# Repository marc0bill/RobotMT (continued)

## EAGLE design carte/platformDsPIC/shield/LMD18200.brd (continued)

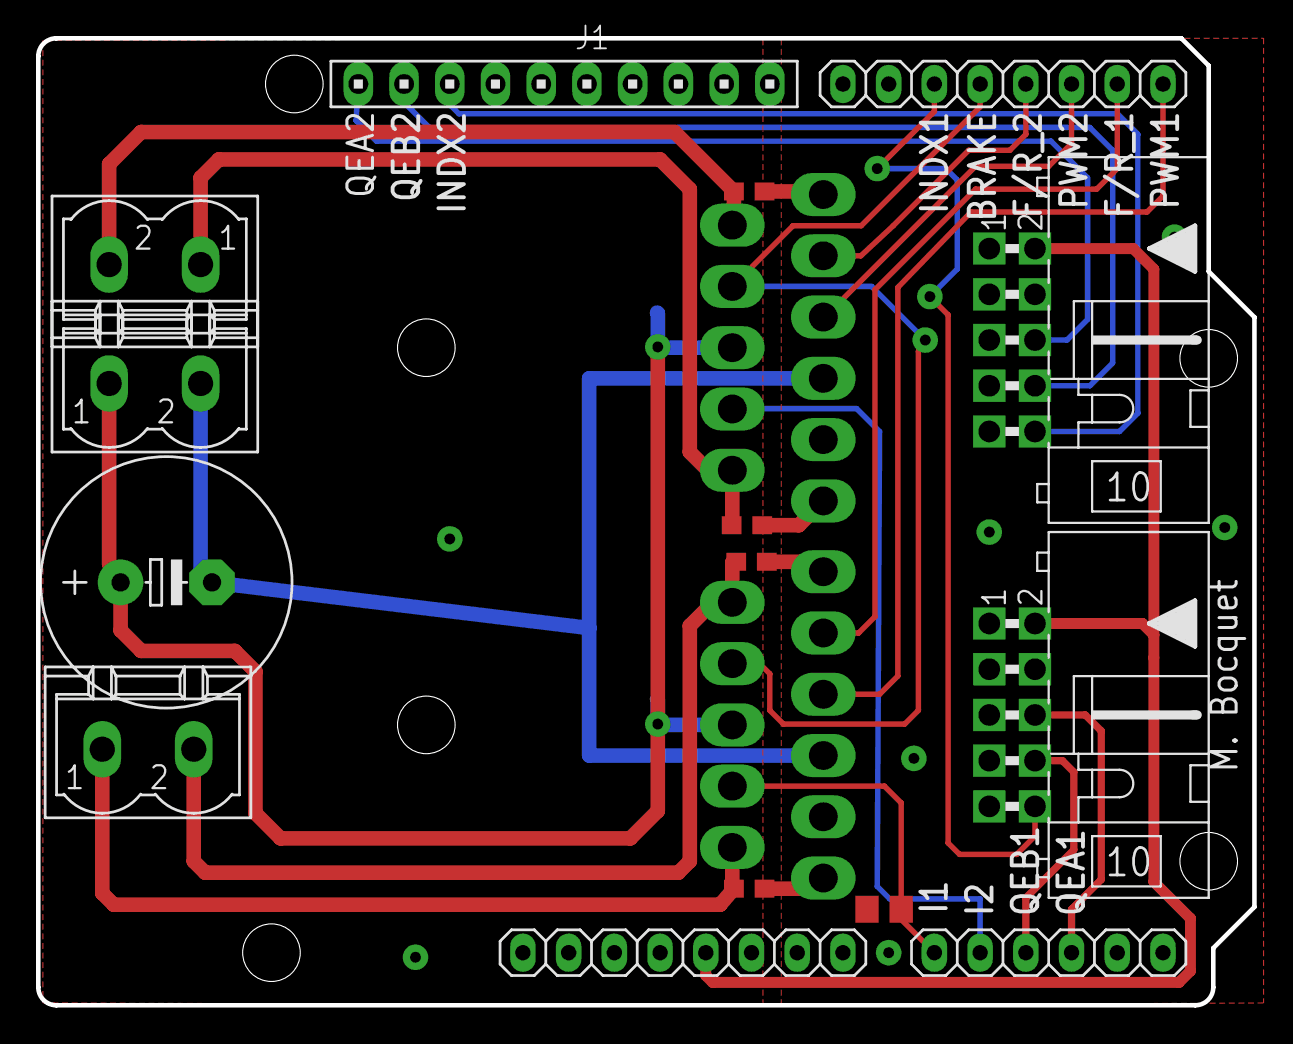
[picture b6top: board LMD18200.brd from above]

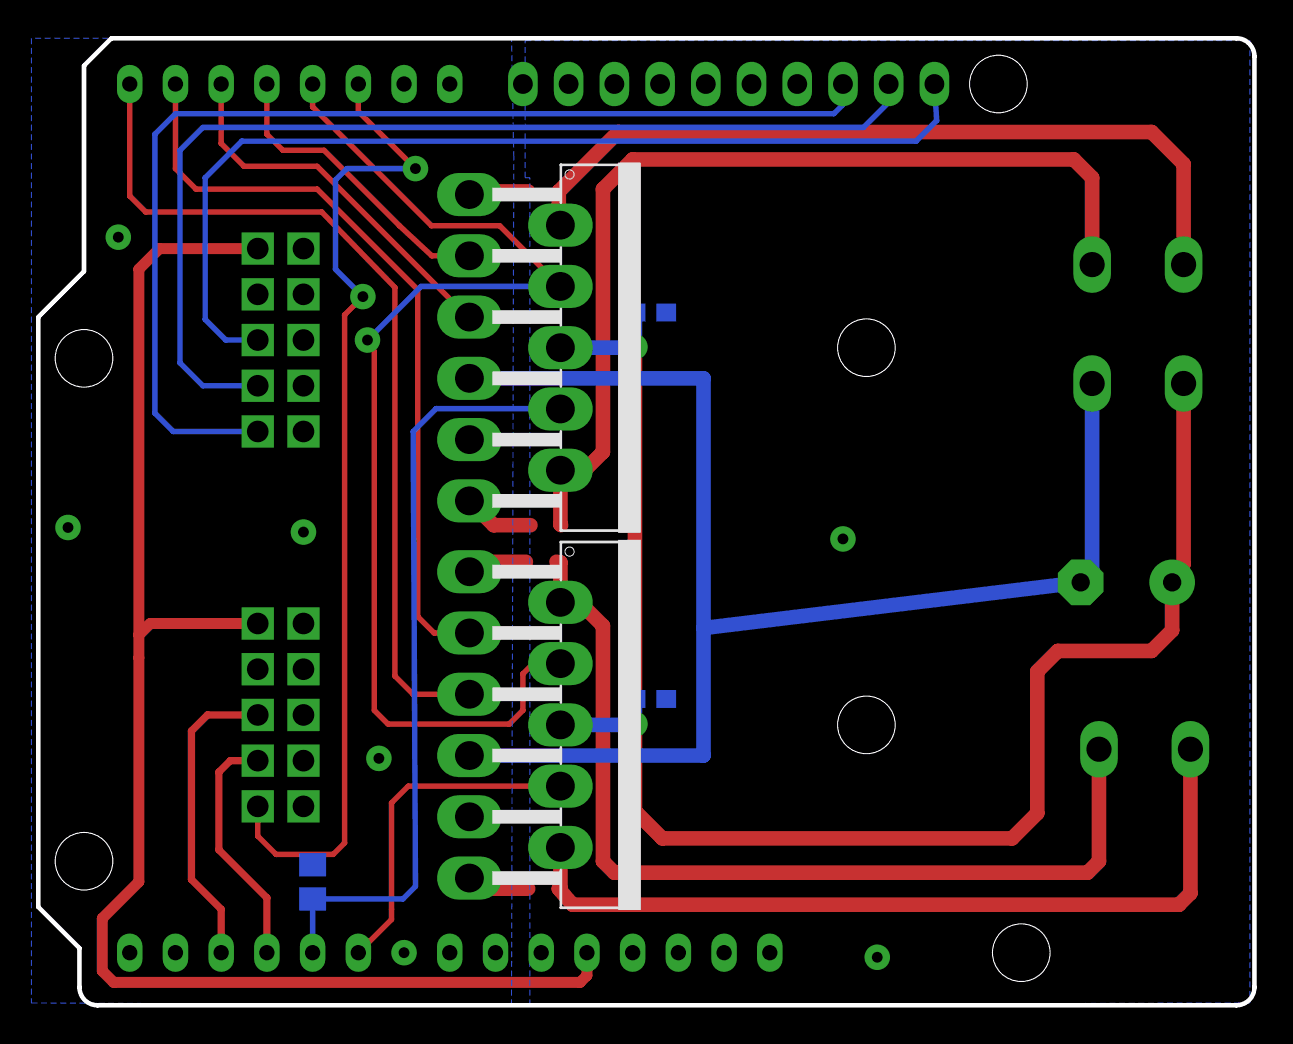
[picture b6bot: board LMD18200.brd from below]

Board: 2 copper layers, 67.6 x 53.7 mm, 20 parts (5 on the bottom side), 25 nets.

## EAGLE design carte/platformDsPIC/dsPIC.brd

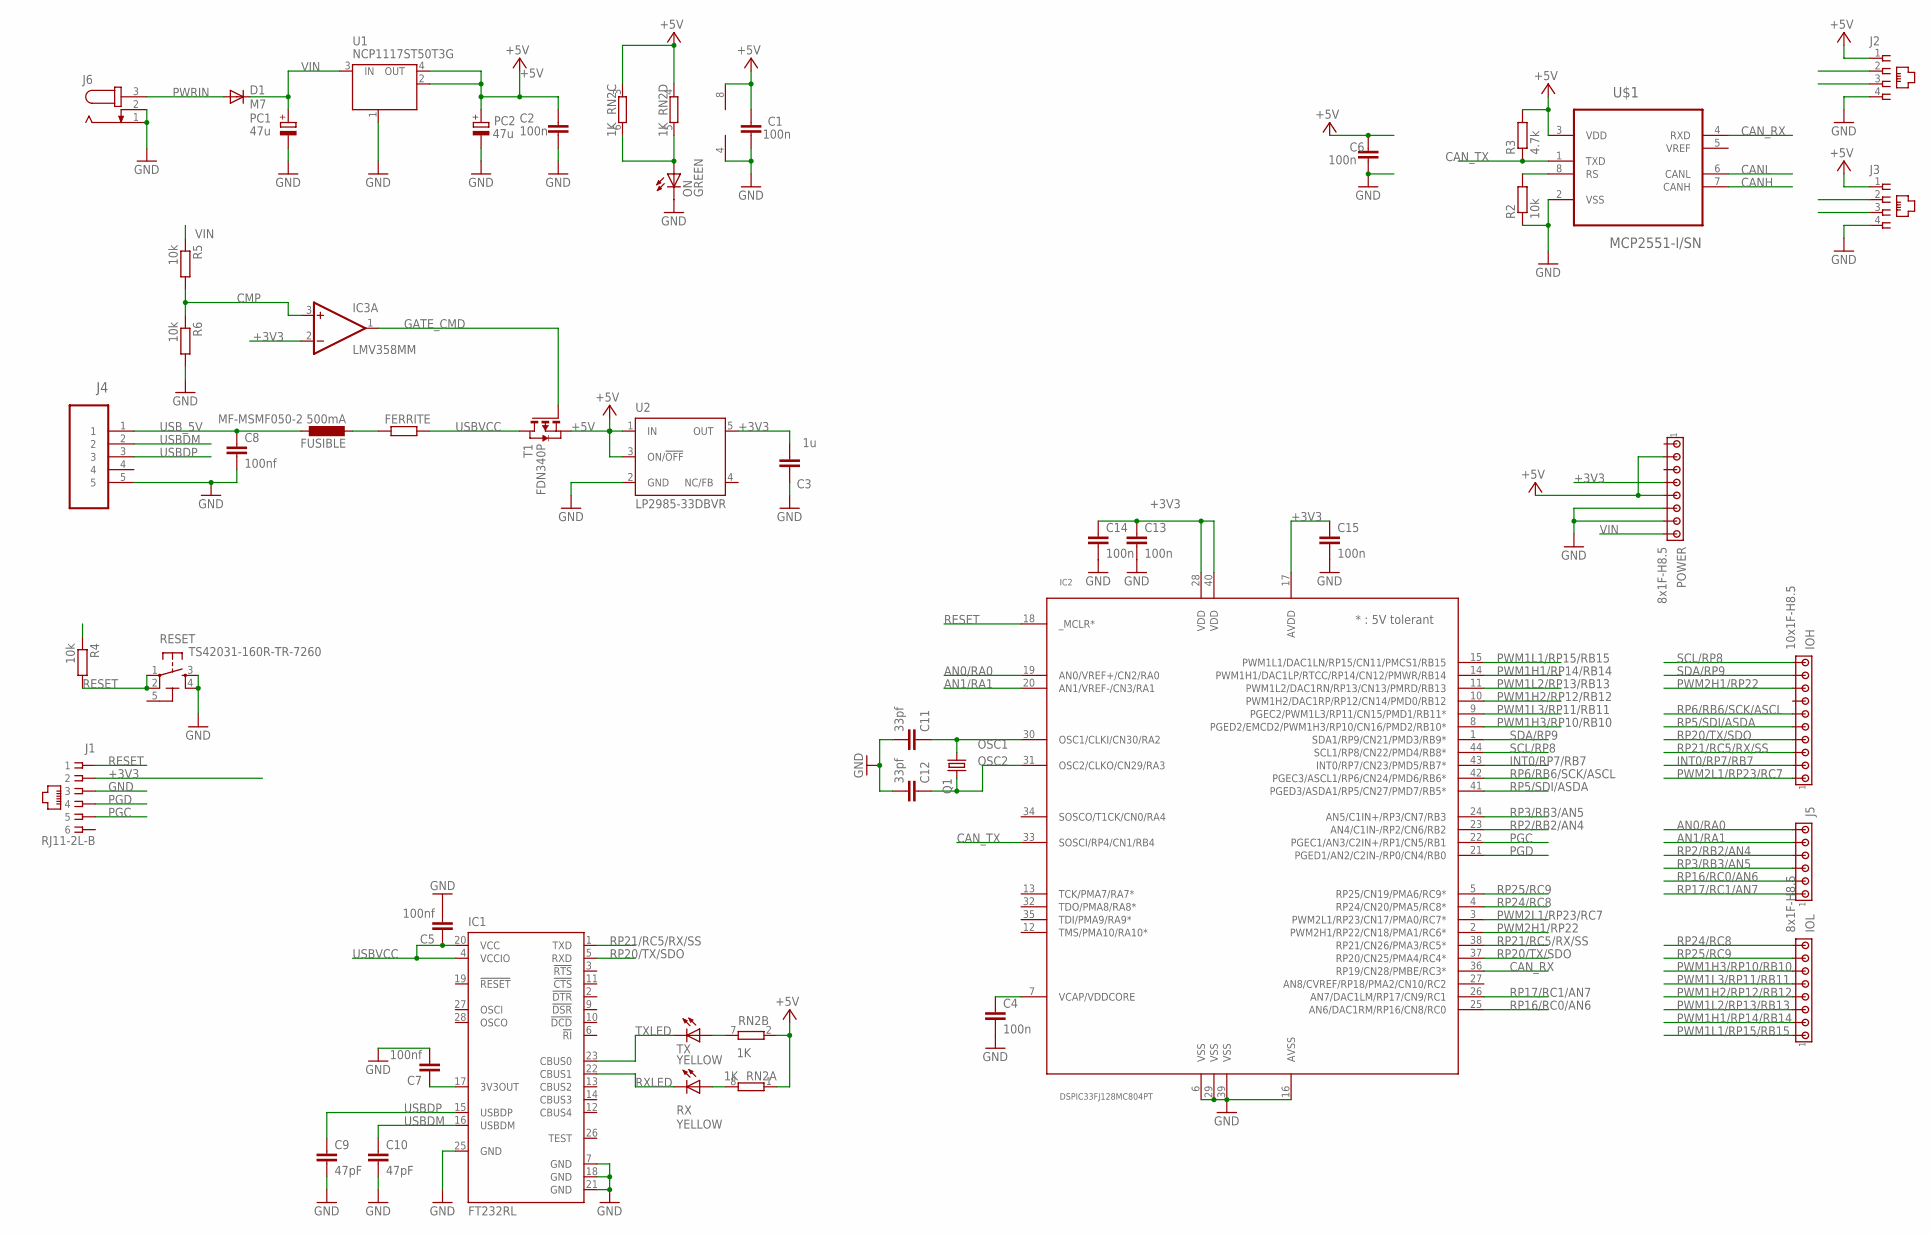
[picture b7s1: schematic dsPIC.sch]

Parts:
C1, C2: 100n; C0603-ROUND
C3: 1u; C0603-ROUND
C4, C6: 100n; C0603K
C5, C7, C8: 100nf; C0603
C9, C10: 47pF; C0603
C11, C12: 33pf; C0603
C13, C14, C15: 100n; C0603
D1: M7; SMB
FERRITE: R-EU_M0805; M0805
FUSIBLE: MF-MSMF050-2 500mA; L1812
IC1: FT232RL; SSOP28
IC2: DSPIC33FJ128MC804PT; TQFP44
IC3: LMV358MM; MSOP08
IOH: 10x1F-H8.5; 10X10MTA
IOL: 8x1F-H8.5; 10X08MTA
J1: RJ11-2L-B; RJ11-NO_SHIELD
J2, J3: 520249-2
J4: 47346-0001; MOLEX_47346-0001
J5: MTA06-100; 10X06MTA
J6: JACK-PLUG0; SPC4077
ON: GREEN; CHIP-LED0805
PC1, PC2: 47u; PANASONIC_D
POWER: 8x1F-H8.5; 10X08MTA
Q1: CRYSTALSM49; SM49
R2, R4, R5, R6: 10k; R0805
R3: 4.7k; R0805
RESET: TS42031-160R-TR-7260; TS42
RN2: 1K; CAY16
RX: YELLOW; CHIP-LED0805
T1: FDN340P; SOT-23
TX: YELLOW; CHIP-LED0805
U1: NCP1117ST50T3G; SOT223
U2: LP2985-33DBVR; SOT23-DBV
U$1: MCP2551-I/SN; SOIC127P600X175-8N

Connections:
5-GND: RESET.5 (5-GND)
+3V3: C3.2, C13.1, C14.1, C15.1, IC2.17 (AVDD), IC2.28 (VDD), IC2.40 (VDD), IC3.2 (-IN), J1.2, POWER.4, R4.1, U2.5 (OUT)
+5V: C1.2, C2.2, C6.2, IC3.8 (V+), J2.1, J3.1, PC2.+, POWER.2, POWER.5, R3.2, RN2.1, RN2.2 (1), RN2.3 (1), RN2.4 (1), T1.2 (S), U1.2 (OUT), U1.4 (OUT), U2.1 (IN), U2.3 (ON/!OFF), U$1.3 (VDD)
AN0/RA0: IC2.19 (AN0/VREF+/CN2/RA0), J5.1 (6)
AN1/RA1: IC2.20 (AN1/VREF-/CN3/RA1), J5.2 (5)
CANH: J2.2, J3.2, U$1.7 (CANH)
CANL: J2.3, J3.3, U$1.6 (CANL)
CAN_RX: IC2.36 (RP19/CN28/PMBE/RC3*), U$1.4 (RXD)
CAN_TX: IC2.33 (SOSCI/RP4/CN1/RB4), R3.1, U$1.1 (TXD)
CMP: IC3.3 (+IN), R5.2, R6.1
GATE_CMD: IC3.1 (OUT), T1.3 (G)
GND: C1.1, C2.1, C3.1, C4.2, C5.2, C6.1, C7.2, C8.2, C9.2, C10.2, C11.2, C12.2, C13.2, C14.2, C15.2, IC1.7 (GND), IC1.18 (GND), IC1.21 (GND), IC1.25 (GND), IC2.6 (VSS), IC2.16 (AVSS), IC2.29 (VSS), IC2.39 (VSS), IC3.4 (V-), J1.3, J2.4, J3.4, J4.5, J6.1, J6.2, ON.C, PC1.-, PC2.-, POWER.6, POWER.7, R2.1, R6.2, RESET.3, RESET.4, U1.1 (GND/ADJ), U2.2 (GND), U$1.2 (VSS)
INT0/RP7/RB7: IC2.43 (INT0/RP7/CN23/PMD5/RB7*), IOH.2
unnamed: RN2.7 (2), TX.A
unnamed: C7.1, IC1.17 (3V3OUT)
unnamed: ON.A, RN2.5 (2), RN2.6 (2)
unnamed: FERRITE.1, FUSIBLE.2
unnamed: C4.1, IC2.7 (VCAP/VDDCORE)
unnamed: RN2.8 (2), RX.A
unnamed: R2.2, U$1.8 (RS)
OSC1: C11.1, IC2.30 (OSC1/CLKI/CN30/RA2), Q1.1
OSC2: C12.1, IC2.31 (OSC2/CLKO/CN29/RA3), Q1.2
PGC: IC2.22 (PGEC1/AN3/C2IN+/RP1/CN5/RB1), J1.5
PGD: IC2.21 (PGED1/AN2/C2IN-/RP0/CN4/RB0), J1.4
PWM1H1/RP14/RB14: IC2.14 (PWM1H1/DAC1LP/RTCC/RP14/CN12/PMWR/RB14), IOL.2
PWM1H2/RP12/RB12: IC2.10 (PWM1H2/DAC1RP/RP12/CN14/PMD0/RB12), IOL.4
PWM1H3/RP10/RB10: IC2.8 (PGED2/EMCD2/PWM1H3/RP10/CN16/PMD2/RB10*), IOL.6
PWM1L1/RP15/RB15: IC2.15 (PWM1L1/DAC1LN/RP15/CN11/PMCS1/RB15), IOL.1
PWM1L2/RP13/RB13: IC2.11 (PWM1L2/DAC1RN/RP13/CN13/PMRD/RB13), IOL.3
PWM1L3/RP11/RB11: IC2.9 (PGEC2/PWM1L3/RP11/CN15/PMD1/RB11*), IOL.5
PWM2H1/RP22: IC2.2 (PWM2H1/RP22/CN18/PMA1/RC6*), IOH.8
PWM2L1/RP23/RC7: IC2.3 (PWM2L1/RP23/CN17/PMA0/RC7*), IOH.1
PWRIN: D1.A, J6.3
RESET: IC2.18 (_MCLR*), J1.1, R4.2, RESET.1, RESET.2
RP2/RB2/AN4: IC2.23 (AN4/C1IN-/RP2/CN6/RB2), J5.3 (4)
RP3/RB3/AN5: IC2.24 (AN5/C1IN+/RP3/CN7/RB3), J5.4 (3)
RP5/SDI/ASDA: IC2.41 (PGED3/ASDA1/RP5/CN27/PMD7/RB5*), IOH.5
RP6/RB6/SCK/ASCL: IC2.42 (PGEC3/ASCL1/RP6/CN24/PMD6/RB6*), IOH.6
RP16/RC0/AN6: IC2.25 (AN6/DAC1RM/RP16/CN8/RC0), J5.5 (2)
RP17/RC1/AN7: IC2.26 (AN7/DAC1LM/RP17/CN9/RC1), J5.6 (1)
RP20/TX/SDO: IC1.5 (RXD), IC2.37 (RP20/CN25/PMA4/RC4*), IOH.4
RP21/RC5/RX/SS: IC1.1 (TXD), IC2.38 (RP21/CN26/PMA3/RC5*), IOH.3
RP24/RC8: IC2.4 (RP24/CN20/PMA5/RC8*), IOL.8
RP25/RC9: IC2.5 (RP25/CN19/PMA6/RC9*), IOL.7
RXLED: IC1.22 (CBUS1), RX.C
SCL/RP8: IC2.44 (SCL1/RP8/CN22/PMD4/RB8*), IOH.10
SDA/RP9: IC2.1 (SDA1/RP9/CN21/PMD3/RB9*), IOH.9
TXLED: IC1.23 (CBUS0), TX.C
USBDM: C10.1, IC1.16 (USBDM), J4.2
USBDP: C9.1, IC1.15 (USBDP), J4.3
USBVCC: C5.1, FERRITE.2, IC1.4 (VCCIO), IC1.20 (VCC), T1.1 (D)
USB_5V: C8.1, FUSIBLE.1, J4.1
VIN: D1.C, PC1.+, POWER.8, R5.1, U1.3 (IN)

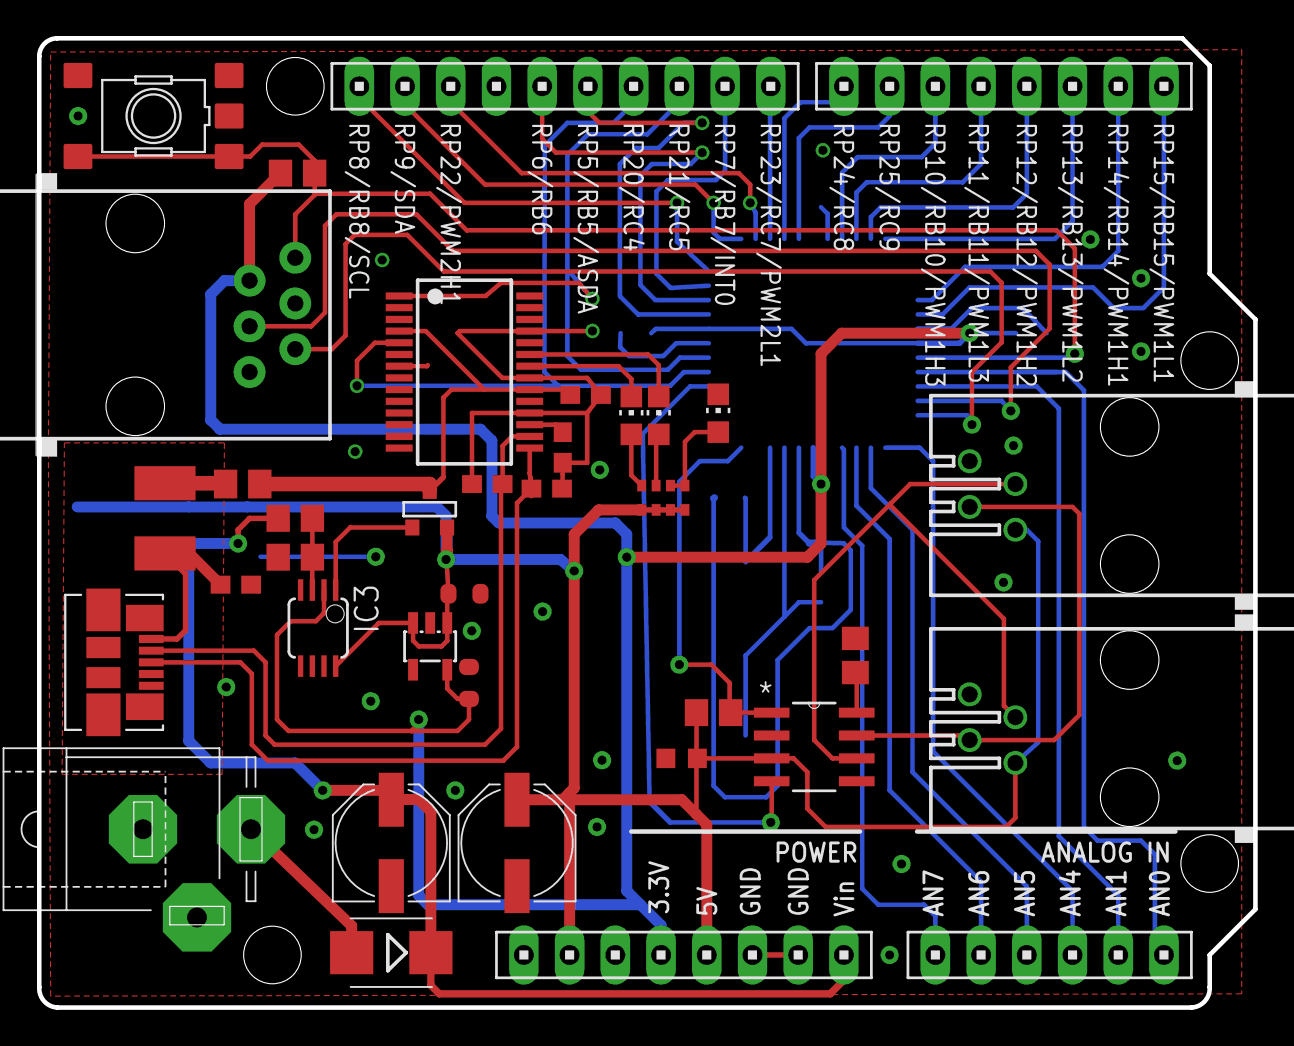
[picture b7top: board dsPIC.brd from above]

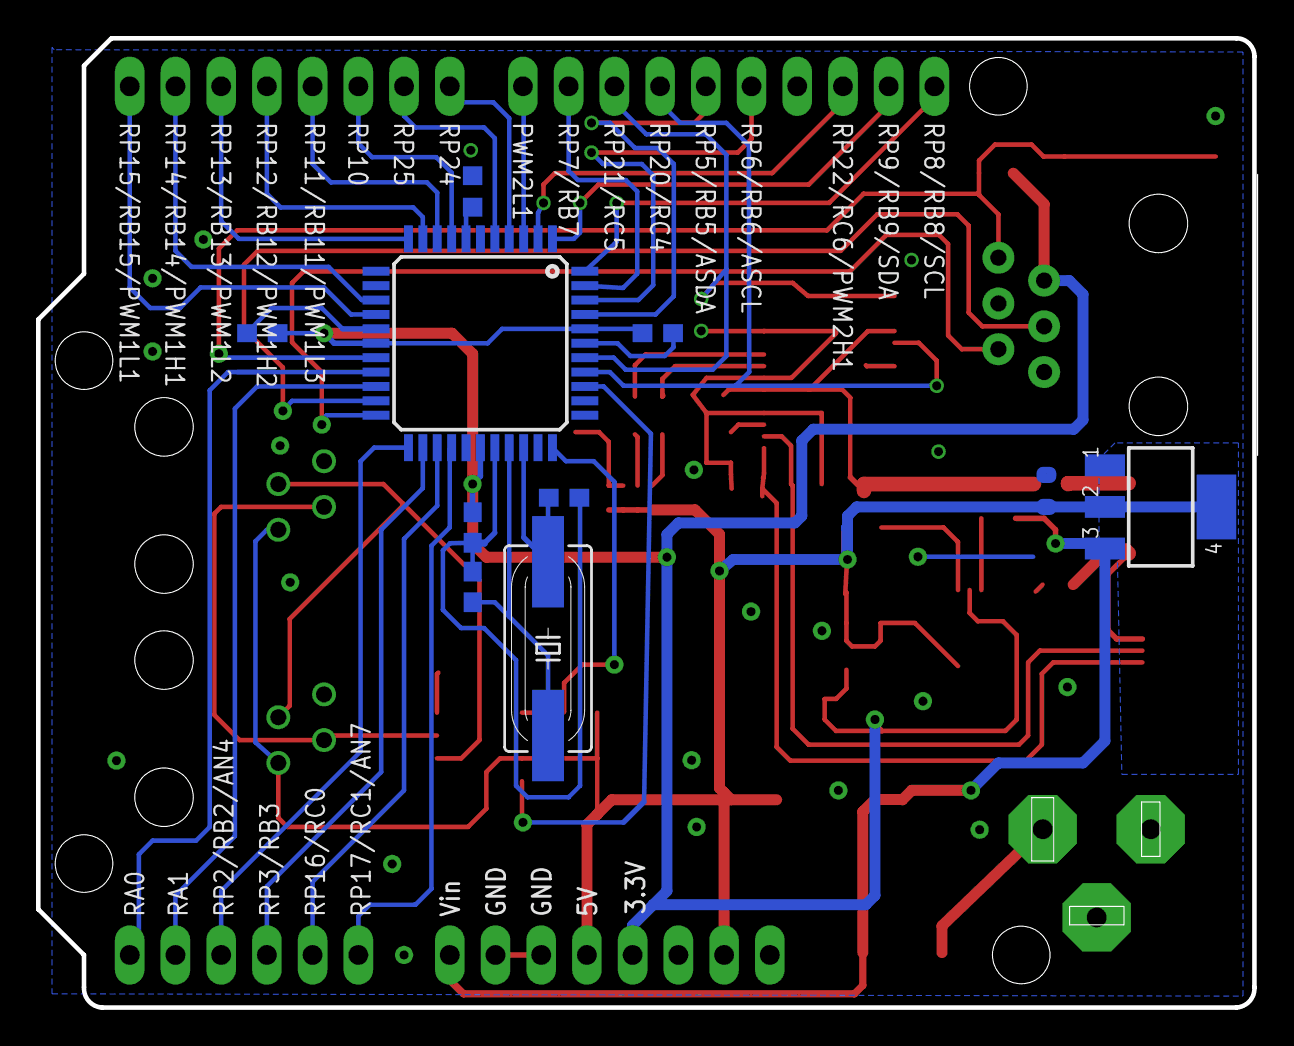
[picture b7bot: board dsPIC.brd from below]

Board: 2 copper layers, 67.6 x 53.8 mm, 47 parts (10 on the bottom side), 52 nets.

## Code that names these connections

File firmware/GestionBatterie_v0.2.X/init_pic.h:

#ifndef _HEADER_H_
#define _HEADER_H_

#ifdef __dsPIC33FJ128MC804__
#include <p33fj128mc804.h>
#endif


#include <libpic30.h>

#define LED_ON 1
#define LED_OFF 0
#define FQUARTZ     4000000	// 4 MHz
#define PLL_N1      0	// 2 	(0.8M<FQuartz/N1<8M)
#define PLL_M       78	// 80 	(100M<FQuartz/N1*M<200M)		//  todo voir si MUL_40 définit dans .h
                        // PLL_M=38, soit FCY=20MHz
                        // PLL_M=78, soit FCY=40MHz
#define PLL_N2      0	// 2	(12.5M<FQuartz*M/(N1*N2)<80M)
				// FOSC=80MHz
				// FCY=40MHz
#define FTYPE       0b011 // Primary oscillator (XT, HS, EC) with PLL (NOSC=0b011)
#define FOSC        (FQUARTZ/(2*2))*80	//(FQUARTZ/(N1*N2))*M
#define FCY         FOSC/2

/* The LEDS and their ports	*/
#define LED1_TRIS		_TRISB15
#define LED2_TRIS		_TRISB14
#define LED3_TRIS		_TRISB13
#define LED4_TRIS		_TRISB12
#define LED5_TRIS		_TRISB11

//#define LED8_TRIS		_TRISC8

#define LED1            _LATB15//_RB15
#define LED2            _LATB14//_RB14
#define LED3            _LATB13//_RB13
#define LED4            _LATB12//_RB12
#define LED5            _LATB11//_RB11

//#define LED8            _LATC8//_RC8

#define LED1_LAT		_LATB15
#define LED2_LAT		_LATB14
#define LED3_LAT		_LATB13
#define LED4_LAT		_LATB12
#define LED5_LAT		_LATB11

//#define LED8_LAT		_LATC8

/*define of muxSEL bits*/
#define muxSEL1_TRIS		TRISC8
#define muxSEL2_TRIS		TRISC7
#define muxSEL3_TRIS		TRISC6

#define muxSEL1         LATC8
#define muxSEL2         LATC7
#define muxSEL3         LATC6

void init_pic(void);

/*
typedef struct muxSEL_TRIS {
  uint16_t muxSEL1_TRIS:1;
  uint16_t muxSEL2_TRIS:1;
  uint16_t muxSEL3_TRIS:1;
} muxSEL_TRIS;

typedef struct muxSEL {
  uint16_t muxSEL1:1;
  uint16_t muxSEL2:1;
  uint16_t muxSEL3:1;
} muxSEL;
*/

#endif

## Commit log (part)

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2018-04-20 update datasheep & ressourceWikiReadme
2018-04-20 gitgnore update
2018-04-20 gitignore update
2018-04-20 update gitignore
2018-04-21 Suppression .DS_Store + backup eagle
2018-04-21 documentation_read_me_1.6
    correction chemin des ressources
2018-04-21 documentation_read_me_1.6.1
2018-04-26 patch jostick
2018-04-26 update python form master
    mise à jours du dossier python provenant du master dans la branche InterfaceUart_eCAN
2018-05-12 platformDsPIC
2018-05-12 un fichier Readme ajouté pour platformDsPIC
2018-05-12 Readme modifié
2018-05-12 read me ajouté
2018-05-18 ajout. projet
2018-05-23 carte alim maj sch/brd
2018-05-23 patch gitignore
2018-05-23 patch gitinore v2
2018-05-23 patch v3 gitinore
2018-05-23 documentation_read_me_1.5
    erreur de chemin du fichier =>deplacement master to interface
2018-05-23 ajout datasheet battery mgmt
2018-05-23 recup_USB_initialcommit
2018-05-24 MAJ carte alim sch/brd
2018-05-24 Changement nom dossier dru eurocircuits
2018-05-24 Deplacement fichier
    Deplacement des fichiers afin de d'ordonner correctement la dossier RobotMT
2018-05-24 Ajout Projet
    4 nodes sont codés dans ce projet
    NODE 1 (unité mère) = écoute tout
    NODE IR = envoie distance du capteur IR
    NODE US = envoie distance du capteur US
    NODE 3= (neutre pour le moment) envoie 4 bytes, ça sera un node à utiliser par les autres groupes (ex :Gestion de batterie)
2018-05-25 eCAN filter
    rajout d'un 3ème filtre
2018-05-25 InterfaceNode_eCAN
    creation/renom dossier de travail
2018-05-25 InterfaceNode_eCAN patch
2018-05-25 Dossier Supprimé
2018-05-25 MAJ ancienne carte alim
2018-05-25 MaJ carte alim : modification labels
2018-05-26 documentation_read_me_1.7
    Mise a jour avec wiki + ajout de uart.h
2018-05-26 Supprime des projets inutiles
2018-05-26 deplacement_read_me1.7
    Deplacement du read me dans un nouveau dossier pour une meilleure structuration du projet
2018-05-27 Create README.md
    Readme de Python
2018-05-27 Create README.md
    Description du code python de Recup_USB
2018-05-28 Modif board + ajout excel
2018-05-28 Ajout datasheet relais
2018-05-29 Add files via upload
    dspic33f- ADC
2018-05-31 Netoyage branche Gestion-Batterie
2018-06-06 alim v1
    Reprise du travail des élèves
2018-06-07 alim v1.0.1
    ajout pdf du brd et sch
2019-04-12 Reconnaissance - v0.0
    Test et demarrage
2019-04-12 FirmwareGestionAlim v0.1
    modif test.c : correction, deux fct main
2019-04-12 Test_commit
2019-04-19 test commit, modification de la todo list
2019-04-26 creation du gant
2019-04-26 version 1 du gant
2019-04-26 ajout du fichier commandes_git
2019-04-26 patch motordrive Mr. Bocquet
2019-04-26 deplacement truc utile
2019-04-26 ajout lien hypertexte pour motion
2019-04-26 ajout de lien utiles
2019-04-26 commit de fin de seance 6
2019-05-03 modification journal de bord jour 3
2019-05-03 Test Tensorflow
2019-05-06 update du journal de bord et des liens utiles
2019-05-06 modif liens utiles
2019-05-06 update journal de bords
2019-05-06 DocUart
2019-05-07 Ajout de l'algo de reconnaissance
2019-05-07 Modification algo de reconnaissance
2019-05-07 fin de seance 8
2019-05-08 gant
2019-05-08 journal de bords
2019-05-09 fin seance... 9?
2019-05-12 Suppression des fichiers inutiles
2019-05-13 Code Firmware Test qui permet la reception de donnée
2019-05-13 on essaie de push
2019-05-13 ajout fichier main
2019-05-13 Ajout du main
2019-05-13 Modification de l'algo de Reconnaissance
2019-05-13 Modification Gantt
2019-05-13 Modification du main
2019-05-13 powerpoint
2019-05-13 presentation
2019-05-13 Recommit
2019-05-13 Modif de la présenttion
2019-05-13 Modif Gantt
2019-05-13 Modif de la présentation
2019-05-13 Ajouté capture_termite
2019-05-13 screen et uart
2019-05-13 screen UART
2019-05-13 fin de journee
2019-05-13 diapo
2019-05-14 modif diapo 2
2019-05-14 creation de la fonction U1Tx_chaine pour transmettre des chaines de carac en UART
2019-05-14 suprresion de bout de codes commentés concernant l'UART
2019-05-14 Modif main + Reconnaisance
2019-05-14 Modification BigBlue.py
2019-05-14 modification de l'UART, ça marche pas des masses, faudra peut etre revenir sur le commit precedent. A voir.
2019-05-15 commit avant de fair en'importe quoi sur le controle moteur, au cas où
2019-05-15 on modifie un truc dans uart.c ligne 130 environ, pas sur que ça marche
2019-05-15 Modification astar.py (commentaires)
2019-05-15 abandon de la reprise du code firmware. Nous commençons à reecirer une V2 (ou V3 à cause d'un soucis de parametre projet) du pwm et de l'uart
2019-05-15 Ajout uart_v2
2019-05-15 Ajout et lien avec le reste dud code de uart
2019-05-15 add uart
2019-05-15 Modif Reconnaissance
2019-05-15 configuration de la PWM V3 inconcluante
2019-05-17 Suppression des dossiers projets MotorDrive_V2 et MotorDrive_V3. Le projet courant est MotorDriveV2 et c'est dans celui-ci que nous continuonq de réecrire les bouts de firmware nécessaires
2019-05-17 re-setup des dossier projets, ne pas faire attention
2019-05-17 commit pour changer de pc, ne pas faire attention
2019-05-17 fin de seance, on s'arrache les cheveux sur le PWM de control moteur
2019-05-18 nouveau uart
2019-05-18 Uart v1.0, prend en compte l'initialisation, Stop et VtsM
2019-05-18 Modif Reconnaissance + main et ajout du programme UART
2019-05-18 J'ai ajouté des commentaires dans l'algo de Reconnaissance
2019-05-18 Re commit
2019-05-18 Modif de Reconnaissance à tester demain
2019-05-18 ajout du code arduino utile afin de tester certaines fonctionnalités car nous n'arrivont pas à nous en sortir avec le PIC
2019-05-18 suppression de la VA du code Arduino
2019-05-18 ajout transmission et début du timer
2019-05-19 Modification Reconnaissance
2019-05-19 Optimisation du code arduino. Ajout de la prise en compte des distance. Pour l'instant la distance est implementer en dur dans le code. Elle sera plus tard recuperer par le capteur de distance ou rec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
2019-05-19 Ajout des commentaires
2019-05-20 commencement du debug de l'uart PIC mais il reste du debug a faire
2019-05-20 timer.c vide, je ne sais pas quoi mettre dedans
2019-05-21 Modif UART et main
2019-05-21 Debug du code de controle moteur par mr.bocquet. Le pwm et l'uart fonctionne a present parfaitement
2019-05-21 Modif main et ReconnaissanceV2
2019-05-21 code de merde pour l'asservissement
2019-05-21 Dossier déplacé
2019-05-21 Modif main
2019-05-21 modif firmware
2019-05-21 Donovan: j'ai repris le code python d'asservissement moteur mais l'architecture ne me plait pas. Je pars sur autre chose. Je fais donc un commit de sauvegarde au cas où je n'arrive pas à m'en sortir 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
2019-05-21 Nouvelle architecture de l'asservissement réalisée. La plupart des erreurs de synthaxes sont corrigées. Reste à voir si cela fonctionne. Nous testerons demain sur le robot
2019-05-22 correction code python
2019-05-22 correction de constantes
2019-05-22 correction des imports
2019-05-22 debug du code python d'sservissement
2019-05-22 Mode 1 mis en place
2019-05-22 correction du code d'asservissement en vue du premier teste robot
2019-05-22 correction mode 1
2019-05-22 ajout de print terminal raspi pour debug
2019-05-22 aaaaarg
2019-05-22 resolution conflit
2019-05-22 fix problem indentation
2019-05-22 correction bug
2019-05-22 debug asserv
2019-05-22 modif asserv raspi
2019-05-22 ecriture d'un premier fichier de teste de com UART entre raspi et PIC
2019-05-22 scripts de teste de com raspi-PIC + update du diapo
2019-05-22 ajout du readme general de notre projet
2019-05-22 doc general
2019-05-22 doc doc doc
2019-05-23 finition des scripts de test de com UAR raspi-pic
2019-05-23 ajout du debut de la doc raspi
2019-05-24 Ajout README Reconnaissance
2019-05-24 script de tst uart raspi
2019-05-24 maj pierre
2019-05-24 première structuration du diapo et doc github asservissement
2019-05-24 modif scripts de tests de com
2019-05-24 Modif README
2019-05-24 dooooooooooooc
2019-05-24 doc y doc
2019-05-24 test format doc
2019-05-24 test format doc2
2019-05-24 encore de la doc
2019-05-25 encore et toujours de la doc
2019-05-25 corerction format doc
2019-05-25 V1 du schema + doc
2019-05-25 doc asservissement et debut du diapo
2019-05-25 reorganisation des dossiers
2019-05-25 test format md
2019-05-25 diapo asservissement
2019-05-25 Modif tensorflow
2019-05-26 Create can_tx
2019-05-26 Create README.md
    GestionBatterie.X FirmwareGestionAlim v0.1
2019-05-26 reprise de la doc d'asserv et ajout de la doc control_moteur de jeremy
2019-05-26 doc asserv
2019-05-26 oups, oublie d'un fichier
2019-05-26 ajout compréhension code
2019-05-26 explication uart dans uart.md+ consigne mode dans controle moteur
2019-05-26 maj Todo list
2019-05-26 rasp - desp dans uart.md
2019-05-26 oubli tourner et reculer
2019-05-26 Ajout de commentaires sur ReconnaissanceV2
2019-05-26 remplacement de la doc asservissement
2019-05-26 modif todo list
2019-05-26 Modif Tensorflow.md
2019-05-26 Test UART Rasp Rasp
2019-05-26 Test UART Rasp Rasp fait
2019-05-26 ajout détail scrypt python
2019-05-26 la doc asservissement est presque finit, plus qu'à corriger encore certaines fautes d'orthographe et d'ajouter l'organigramme de l'algorithme
2019-05-26 corrrection pour format md
2019-05-26 corrrection pour format md encore
2019-05-26 reprise du logigramme de l'algo asservissement + intergration dans la doc
2019-05-26 reprise des doc
2019-05-27 regorga des dossiers
2019-05-27 correction
2019-05-27 modif sur la rasp
2019-05-27 correction francais controle moteur
2019-05-27 capture rasp
2019-05-27 Capture
2019-05-27 ajout print ratio
2019-05-27 Modif UART
2019-05-27 doc uart
2019-05-27 ajout de photos
2019-05-27 modif commande rasp
2019-05-27 correction de l'envoie de vitesse negative lors de la phase d'avancement
2019-05-27 correction orthographe jeremy
2019-05-27 modif pythin vitesse min
2019-05-27 modif pythin bottle
2019-05-27 schema controle moteur
2019-05-27 Ajout capture
2019-05-27 python vitesse max
2019-05-27 add stop
2019-05-27 refrigerator
2019-05-27 Rename Données_tracées_de_manière_instantanée.py to Données_tracées_instantanée.py
2019-05-27 Rename Données_tracées_instantanée.py to Données_tracées_instantanées.py
2019-05-28 ajout de teste dans README python
2019-05-29 Rename README.md to README.mc
2019-05-29 Rename README.mc to README2.md
2019-05-30 Rename simple_rx_test.py to can_rx_final_app.py
2019-06-02 Rename Sauvegarde_données_sur_excel_tracer.py to Données_tracées_instantanées_2.py
